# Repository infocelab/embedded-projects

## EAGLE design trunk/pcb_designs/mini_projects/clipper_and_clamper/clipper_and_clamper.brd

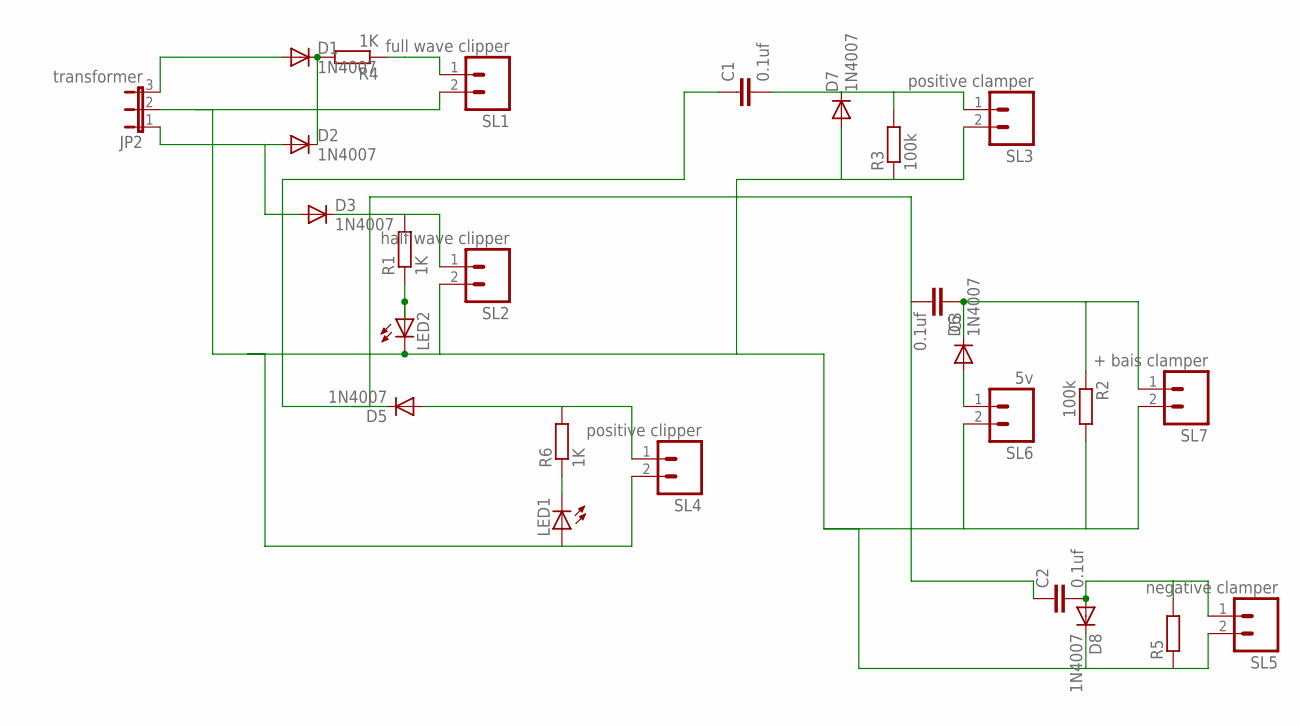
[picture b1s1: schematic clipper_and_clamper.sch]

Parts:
C1, C2, C3: 0.1uf; C2.5-3
D1, D2, D3, D5, D6, D7, D8: 1N4007; DO41-10
JP2: transformer; JP2
LED1, LED2: LED3MM
R1, R4, R6: 1K; 0204/7
R2, R3: 100k; 0204/7
R5: R0204/7; 0204/7
SL1: full wave clipper; 02P
SL2: half wave clipper; 02P
SL3: positive clamper; 02P
SL4: positive clipper; 02P
SL5: negative clamper; 02P
SL6: 5v; 02P
SL7: + bais clamper; 02P

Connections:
unnamed: D1.C, D2.C, R4.2
unnamed: D1.A, JP2.3
unnamed: C1.1, C2.1, C3.2, D2.A, D3.A, D5.C, JP2.1
unnamed: D7.A, D8.C, JP2.2, LED1.A, LED2.K (C), R2.2, R3.1, R5.1, SL1.2, SL2.2, SL3.2, SL4.2, SL5.2, SL6.2, SL7.2
unnamed: R4.1, SL1.1
unnamed: D3.C, R1.2, SL2.1
unnamed: LED2.A, R1.1
unnamed: C2.2, D8.A, R5.2, SL5.1
unnamed: D5.A, R6.2, SL4.1
unnamed: LED1.K (C), R6.1
unnamed: C1.2, D7.C, R3.2, SL3.1
unnamed: D6.A, SL6.1
unnamed: C3.1, D6.C, R2.1, SL7.1

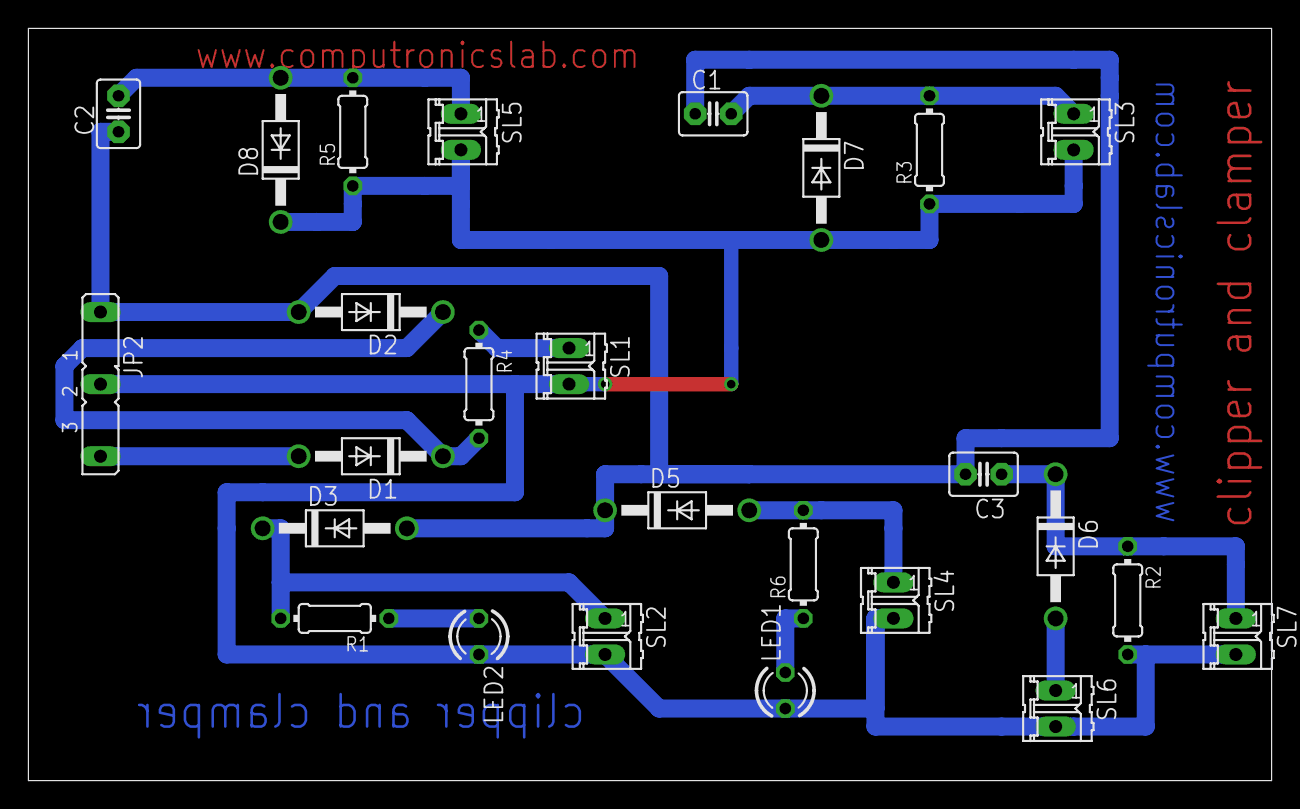
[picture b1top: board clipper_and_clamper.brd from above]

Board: 2 copper layers, 87.6 x 53.0 mm, 26 parts (0 on the bottom side), 13 nets.

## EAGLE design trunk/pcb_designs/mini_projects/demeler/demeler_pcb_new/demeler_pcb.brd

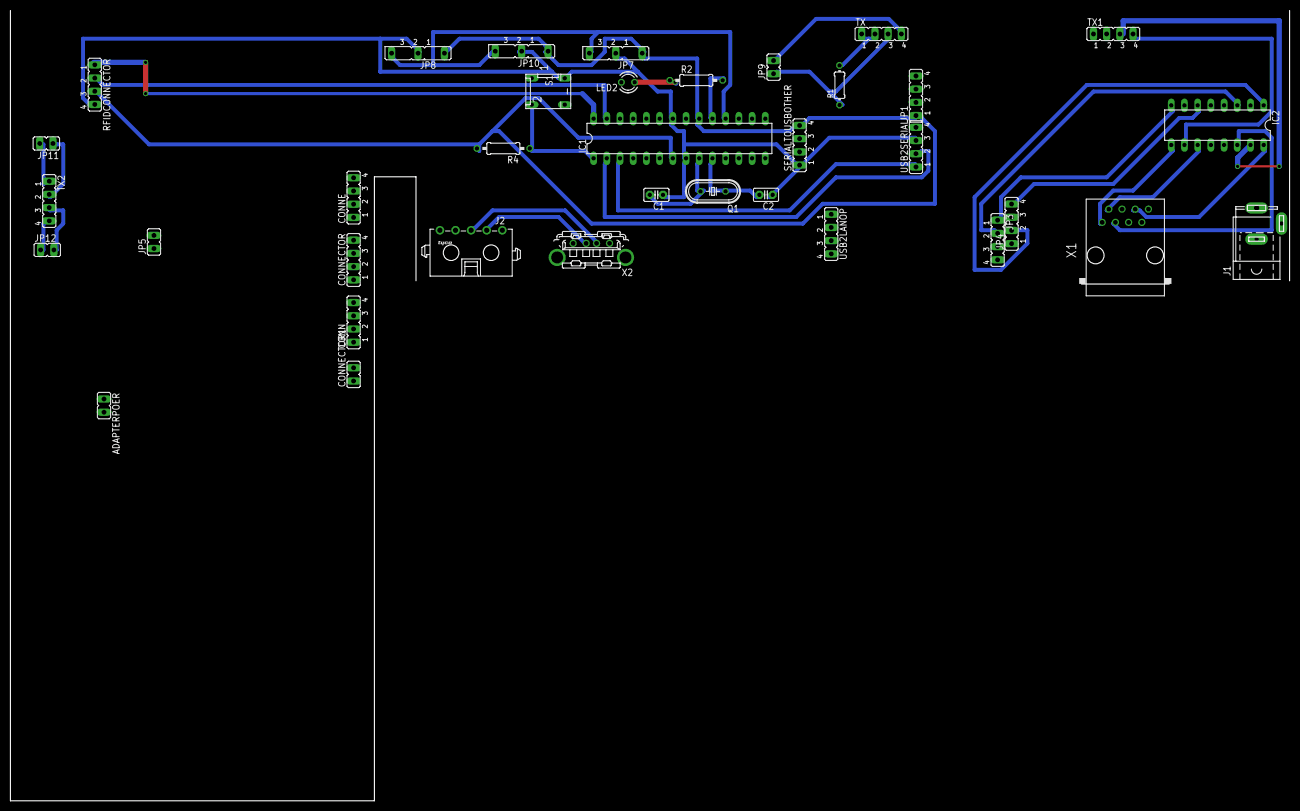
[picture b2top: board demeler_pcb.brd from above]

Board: 2 copper layers, 246.0 x 152.0 mm, 36 parts (0 on the bottom side), 31 nets.

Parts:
ADAPTERPOER: JP1
C1, C2: 22pf; C2.5-2
CONN: JP4
CONNE: JP4
CONNECTOR: JP4
CONNECTOR1: JP1
IC1: ATMEGA328; DIL28-3
IC2: L293D; DIL16
J1: SPC4077
J2: 1445055-5
JP1, JP3, JP4: JP4
JP5, JP9, JP11, JP12: JP1
JP7, JP8, JP10: JP2
LED2: LED3MM
Q1: 16MHZ; HC49/S
R1: 0204/7
R2: 330R; 0207/10
R4: 10K; 0207/10
RFIDCONNECTOR: JP4
S1: DP-02
SERIALTOUSBOTHER: JP4
TX, TX1, TX2: JP4
USB2LANOP, USB2SERIAL: JP4
X1: RJ45-6X; RJ45-NO-SHIELD
X2: KUSBVX

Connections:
+5V: IC1.7, IC1.20, JP1.1, JP7.1, JP8.1, JP10.1, R4.2, RFIDCONNECTOR.3, SERIALTOUSBOTHER.4
GND: C1.1, C2.1, IC1.8, IC1.22, JP7.2, JP8.2, JP10.2, LED2.K, RFIDCONNECTOR.4, S1.4, SERIALTOUSBOTHER.1, USB2SERIAL.3
unnamed: C1.2, IC1.9, Q1.2
unnamed: C2.2, IC1.10, Q1.1
unnamed: IC1.3, USB2SERIAL.1
unnamed: J2.3, X2.3
unnamed: IC1.19, R2.2
unnamed: IC2.9, X1.1
unnamed: IC2.11, X1.2
unnamed: IC2.14, X1.3
unnamed: IC2.16, X1.6
unnamed: IC2.8, JP3.1
unnamed: IC2.6, JP4.4
unnamed: IC2.3, JP3.2
unnamed: IC2.1, JP4.2
unnamed: IC2.10, TX1.4
unnamed: IC2.15, TX1.3
unnamed: IC1.2, USB2SERIAL.2
unnamed: R1.2, TX.1, TX.2
unnamed: JP9.1, R1.1, TX.3
unnamed: J2.2, X2.2
unnamed: JP9.2, TX.4
unnamed: IC1.27, RFIDCONNECTOR.2
unnamed: IC1.28, RFIDCONNECTOR.1
unnamed: IC1.18, JP7.3, JP8.3, JP10.3
unnamed: JP11.2, TX2.1
unnamed: JP11.1, TX2.2
unnamed: JP12.2, TX2.3
unnamed: JP12.1, TX2.4
unnamed: IC1.1, R4.1, S1.2
unnamed: LED2.A, R2.1

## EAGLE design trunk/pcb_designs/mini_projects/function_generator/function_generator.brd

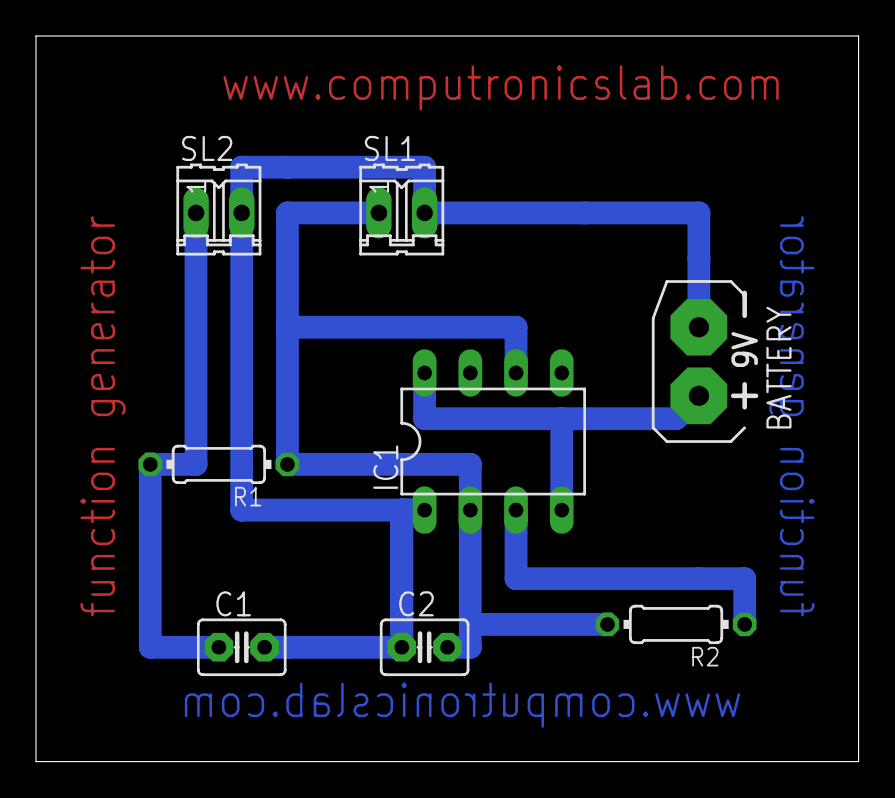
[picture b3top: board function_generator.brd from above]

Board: 2 copper layers, 45.7 x 40.3 mm, 8 parts (0 on the bottom side), 5 nets.

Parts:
BATTERY: 9v; AB9V
C1: .2uf; C2.5-3
C2: .1uf; C2.5-3
IC1: NE555; DIL-08
R1: 100K; 0204/7
R2: 47K; 0204/7
SL1: square wave; 02P
SL2: triangle wave; 02P

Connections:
unnamed: BATTERY.+, IC1.4, IC1.8
unnamed: C2.2, IC1.2, IC1.6, R1.1, R2.2, SL1.1
unnamed: BATTERY.-, C1.2, C2.1, IC1.1, SL1.2, SL2.2
unnamed: IC1.3, R2.1
unnamed: C1.1, R1.2, SL2.1

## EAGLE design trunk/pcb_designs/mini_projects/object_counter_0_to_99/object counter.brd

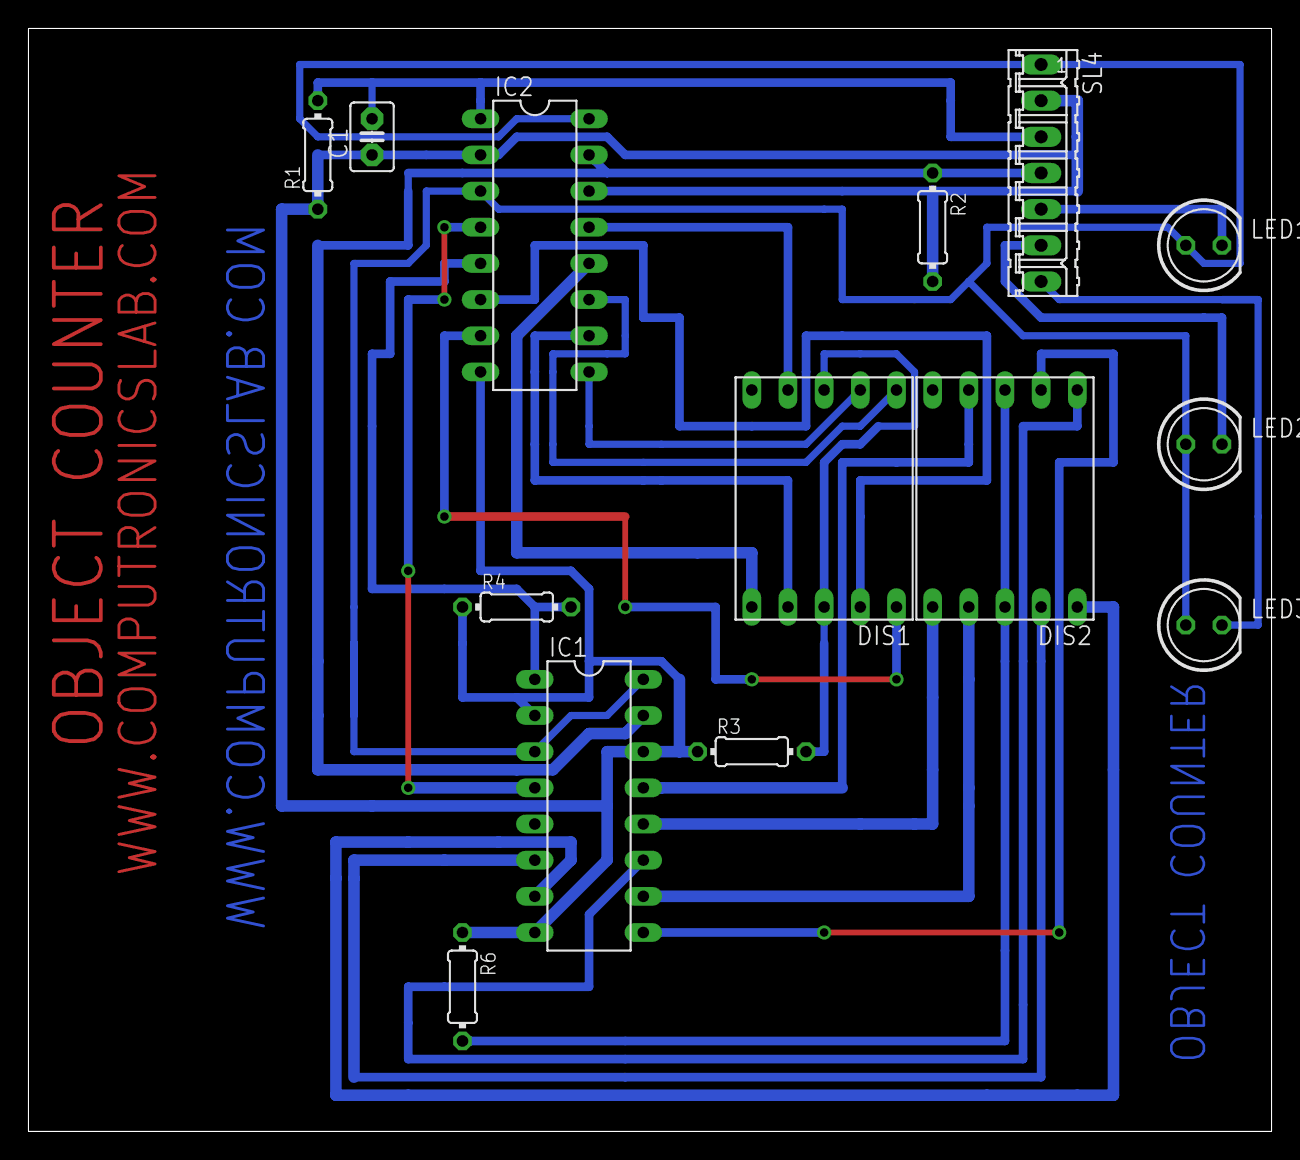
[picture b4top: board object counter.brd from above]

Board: 2 copper layers, 87.3 x 77.5 mm, 14 parts (0 on the bottom side), 25 nets.

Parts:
C1: C2.5-3
DIS1, DIS2: COMMON CATHODE; HDSP-M
IC1, IC2: 4033; DIL16
LED1, LED2, LED3: LED5MM
R1, R4: 33K; 0204/7
R2: 47K; 0204/7
R3, R6: 470E; 0204/7
SL4: 07P

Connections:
unnamed: C1.1, IC1.2, IC1.8, IC1.14, IC2.2, IC2.8, IC2.14, R1.1, R2.2, R3.1, R4.1, R6.1, SL4.2
unnamed: DIS1.3, DIS1.8, R3.2
unnamed: C1.2, IC2.1, R1.2, SL4.3
unnamed: DIS1.7, IC2.10
unnamed: DIS1.6, IC2.12
unnamed: DIS1.4, IC2.13
unnamed: DIS1.2, IC2.9
unnamed: DIS1.1, IC2.11
unnamed: DIS1.9, IC2.6
unnamed: DIS1.10, IC2.7
unnamed: IC1.15, IC2.15, R2.1, SL4.4
unnamed: IC1.3, IC1.16, IC2.3, IC2.16, LED1.A, LED2.A, LED3.A, SL4.1
unnamed: DIS2.3, DIS2.8, R6.2
unnamed: IC1.1, IC2.5, R4.2
unnamed: DIS2.7, IC1.10
unnamed: DIS2.6, IC1.12
unnamed: DIS2.4, IC1.13
unnamed: DIS2.2, IC1.9
unnamed: DIS2.1, IC1.11
unnamed: DIS2.9, IC1.6
unnamed: DIS2.10, IC1.7
unnamed: LED1.K, SL4.5
unnamed: LED2.K, SL4.6
unnamed: LED3.K, SL4.7
V-: IC1.4, IC2.4

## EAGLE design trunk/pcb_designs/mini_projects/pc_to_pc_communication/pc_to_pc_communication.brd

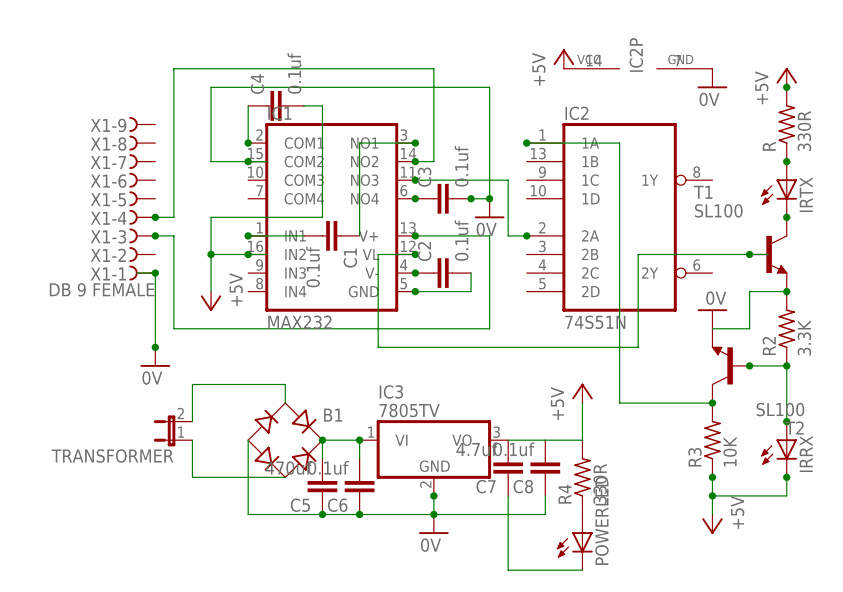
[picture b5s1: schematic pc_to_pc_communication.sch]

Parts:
B1: B-DIL
C1, C2, C3, C4, C6, C8: 0.1uf; C2.5-3
C5: 470uf; C2.5-3
C7: 4.7uf; C2.5-3
IC1: MAX232; DIL16
IC2: 74S51N; DIL14
IC3: 7805TV; TO220V
IRRX: LED3MM
IRTX: LED3MM
POWERLED: LED3MM
R, R4: 330R; 0204/7
R2: 3.3K; 0204/7
R3: 10K; 0204/7
T1, T2: SL100; TO5
TRANSFORMER: JP1E; JP1
X1: DB 9 FEMALE; H2M09ST

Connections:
0V: B1.-, C3.2, C5.1, C6.1, C7.1, C8.1, IC1.15 (COM2), IC2.7 (GND), IC3.2 (GND), POWERLED.K (C), R2.2, T1.1 (E), T2.1 (E), X1.1
+5V: C4.2, C7.2, C8.2, IC1.16 (IN2), IC2.14 (VCC), IC3.3 (VO), IRRX.K (C), R.2, R3.1, R4.2
unnamed: C1.2, IC1.1 (IN1)
unnamed: C1.1, IC1.3 (NO1)
unnamed: C2.1, IC1.4 (V-)
unnamed: C2.2, IC1.5 (GND)
unnamed: C3.1, IC1.6 (NO4)
unnamed: IRTX.K (C), T1.3 (C)
unnamed: C4.1, IC1.2 (COM1)
unnamed: IRTX.A, R.1
unnamed: IC1.13 (V+), X1.3
unnamed: IC1.14 (NO2), X1.4
unnamed: IC1.11 (NO3), IC2.2 (2A)
unnamed: IC1.12 (VL), T1.2 (B)
unnamed: IRRX.A, R2.1, T2.2 (B)
unnamed: IC2.1 (1A), R3.2, T2.3 (C)
unnamed: B1.+, C5.2, C6.2, IC3.1 (VI)
unnamed: B1.AC1, TRANSFORMER.2
unnamed: B1.AC2, TRANSFORMER.1
unnamed: POWERLED.A, R4.1

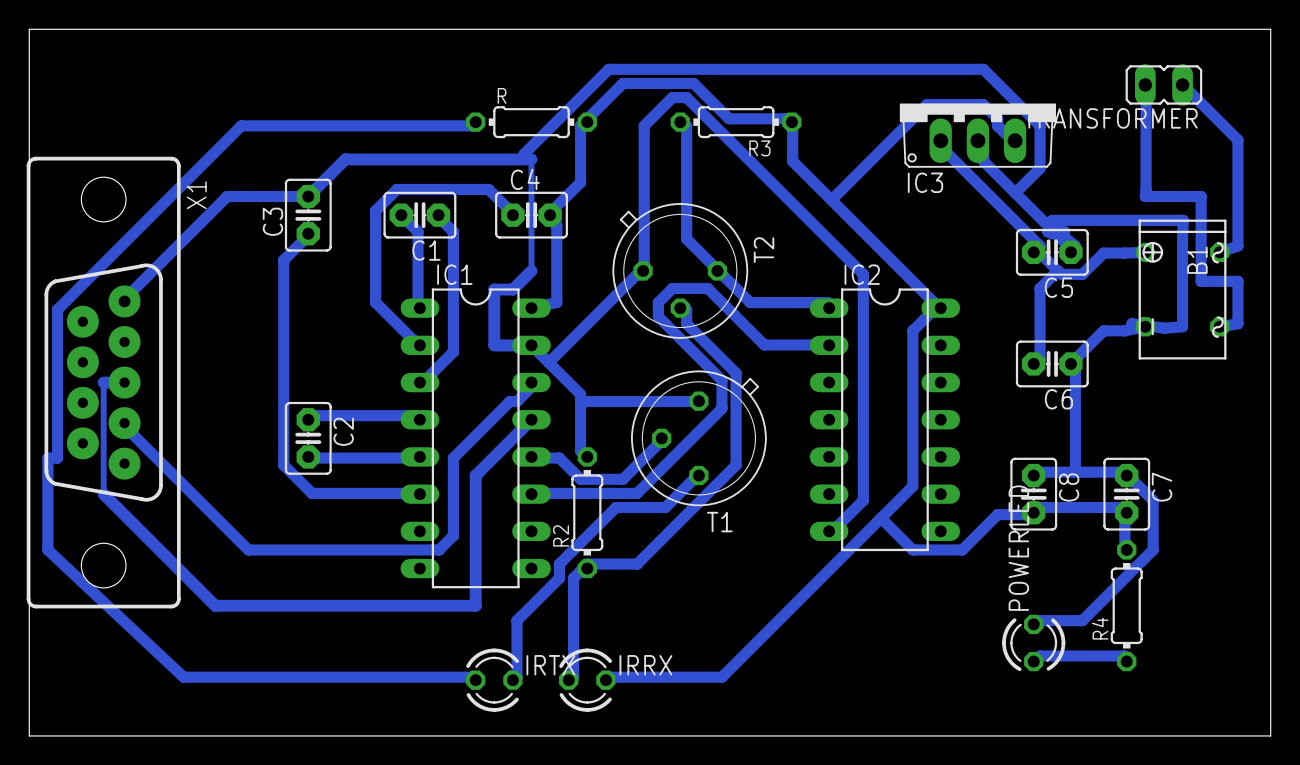
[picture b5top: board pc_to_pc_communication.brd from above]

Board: 2 copper layers, 84.8 x 48.2 mm, 23 parts (0 on the bottom side), 20 nets.

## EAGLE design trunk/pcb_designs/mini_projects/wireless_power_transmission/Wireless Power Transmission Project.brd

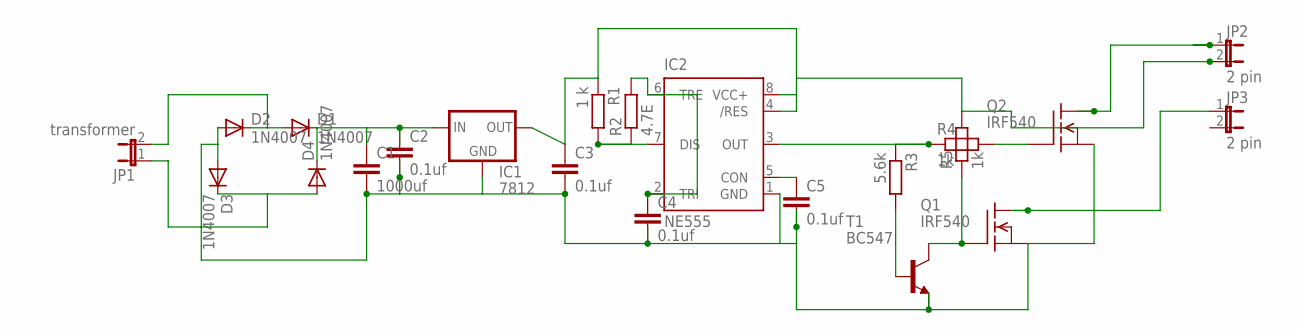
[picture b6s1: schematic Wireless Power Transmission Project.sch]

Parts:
C1: 1000uf; C2.5-5
C2, C3, C4: 0.1uf; C2.5-5
C5: 0.1uf; C2.5-3
D1, D2, D3, D4: 1N4007; DO41-10
IC1: 7812; 78XXL
IC2: NE555; DIL-08
JP1: transformer; JP1
JP2, JP3: 2 pin; JP1
Q1, Q2: IRF540; TO220
R1: 1 k; 0204/7
R2: 4.7E; 0204/7
R3: 5.6k; 0204/7
R4, R5: 1k; 0204/7
T1: BC547; TO92

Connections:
unnamed: D1.A, D2.C, JP1.2
unnamed: C1.2, C2.2, C3.2, C4.2, C5.2, D2.A, D3.A, IC1.GND, IC2.1 (GND), Q1.3 (S), Q2.3 (S), T1.1 (E)
unnamed: D3.C, D4.A, JP1.1
unnamed: C1.1, C2.1, D1.C, D4.C, IC1.IN
unnamed: C5.1, IC2.5 (CON)
unnamed: IC2.3 (OUT), R3.1, R4.1
unnamed: C3.1, IC1.OUT, IC2.4 (/RES), IC2.8 (VCC+), JP2.2, R1.1, R5.2
unnamed: IC2.7 (DIS), R1.2, R2.1
unnamed: R3.2, T1.2 (B)
unnamed: C4.1, IC2.2 (TRI), IC2.6 (TRE), R2.2
unnamed: Q1.1 (G), R5.1, T1.3 (C)
unnamed: Q2.1 (G), R4.2
unnamed: JP2.1, Q2.2 (D)
unnamed: JP3.1, Q1.2 (D)

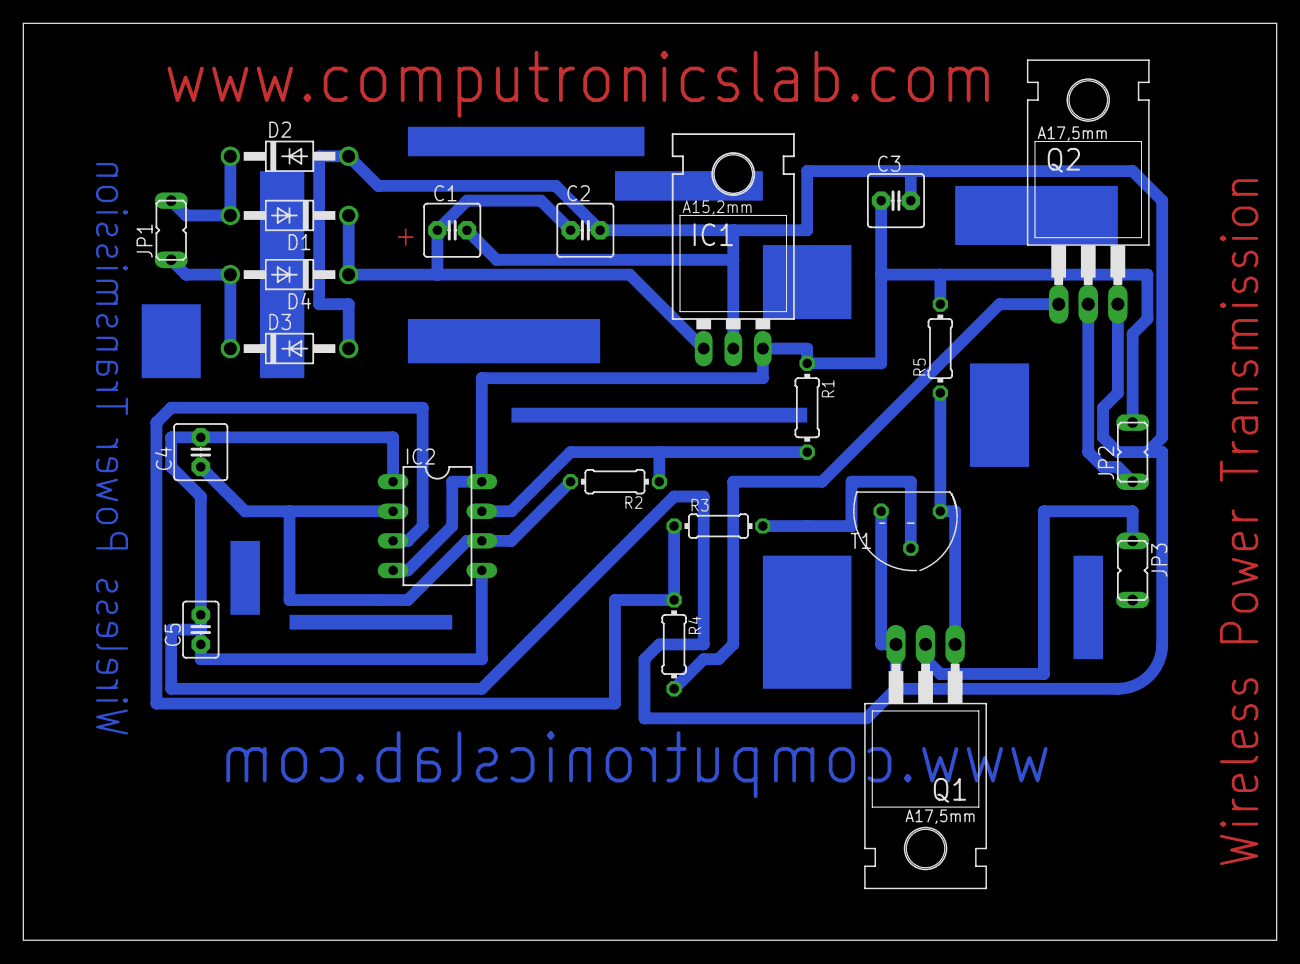
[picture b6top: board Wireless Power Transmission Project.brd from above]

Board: 2 copper layers, 107.6 x 78.7 mm, 22 parts (0 on the bottom side), 14 nets.

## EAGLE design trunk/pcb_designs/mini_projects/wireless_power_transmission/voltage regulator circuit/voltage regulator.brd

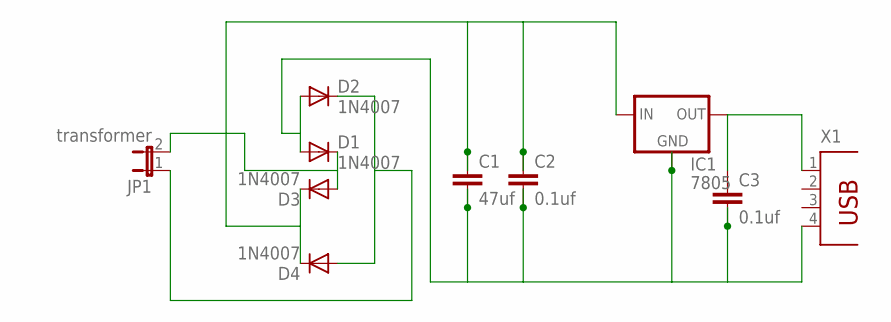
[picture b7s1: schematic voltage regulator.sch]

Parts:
C1: 47uf; C2.5-3
C2, C3: 0.1uf; C2.5-3
D1, D2, D3, D4: 1N4007; DO41-10
IC1: 7805; 78XXL
JP1: transformer; JP1
X1: PN87520

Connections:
unnamed: C1.2, C2.2, C3.2, D1.A, D2.A, IC1.GND, X1.4
unnamed: C1.1, C2.1, D3.C, D4.C, IC1.IN
unnamed: D2.C, D4.A, JP1.1
unnamed: D1.C, D3.A, JP1.2
unnamed: C3.1, IC1.OUT, X1.1

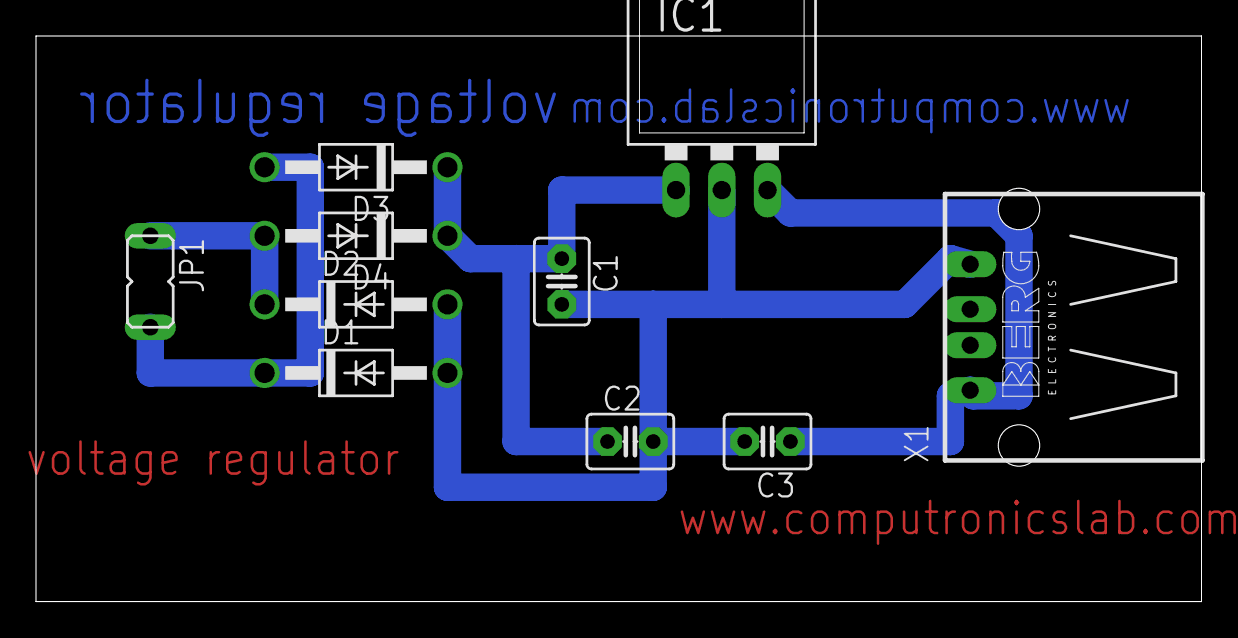
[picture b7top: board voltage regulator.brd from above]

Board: 2 copper layers, 64.8 x 31.4 mm, 10 parts (0 on the bottom side), 5 nets.

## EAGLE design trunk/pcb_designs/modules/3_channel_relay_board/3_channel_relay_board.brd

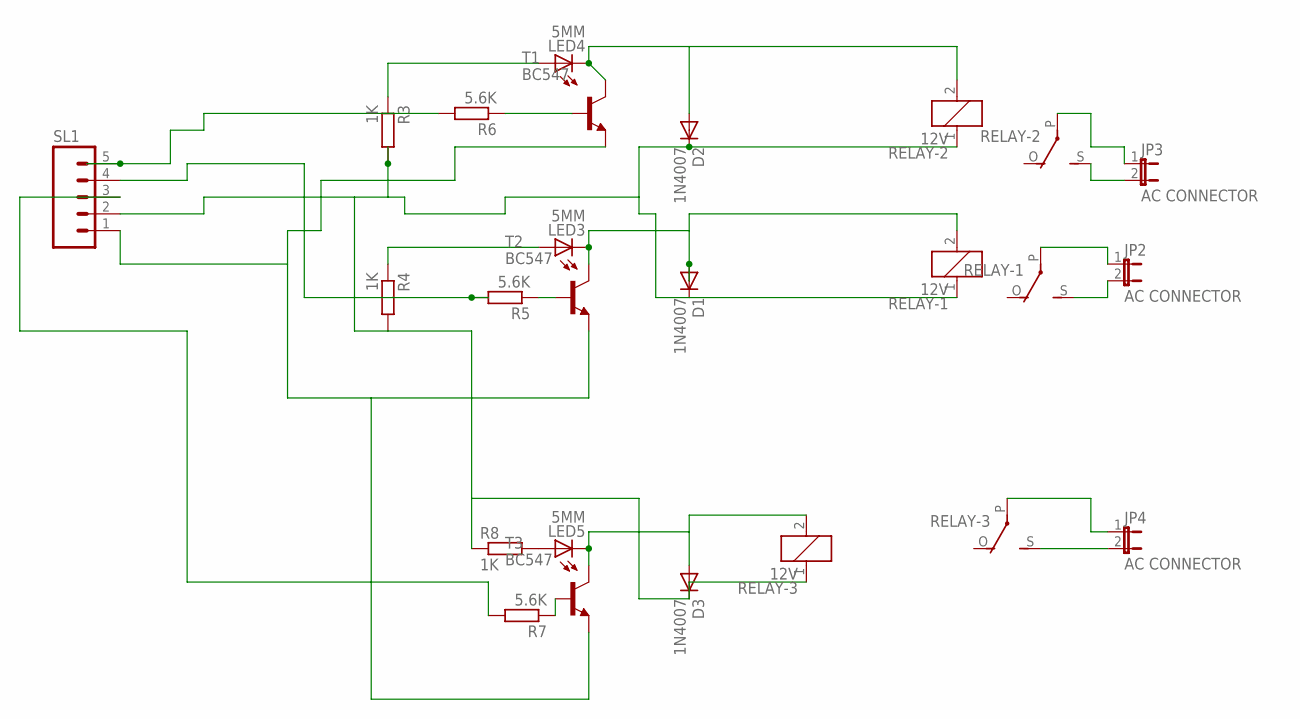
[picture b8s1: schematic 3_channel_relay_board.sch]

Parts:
D1, D2, D3: 1N4007; DO41-10
JP2, JP3, JP4: AC CONNECTOR; JP1
LED3, LED4, LED5: 5MM; LED5MM
R3, R4, R8: 1K; 0204/7
R5, R6, R7: 5.6K; 0204/7
RELAY-1, RELAY-2, RELAY-3: 12V; G5LE
SL1: M05; 05P
T1, T2, T3: BC547; TO92

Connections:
unnamed: D1.A, LED3.K (C), RELAY-1.2, T2.3 (C)
unnamed: SL1.1, T1.1 (E), T2.1 (E), T3.1 (E)
unnamed: R7.2, SL1.3
unnamed: R6.2, SL1.5
unnamed: D1.C, D2.C, D3.C, R3.2, R4.2, R8.1, RELAY-1.1, RELAY-2.1, RELAY-3.1, SL1.2
unnamed: R6.1, T1.2 (B)
unnamed: R5.1, T2.2 (B)
unnamed: LED3.A, R4.1
unnamed: LED4.A, R3.1
unnamed: JP2.2, RELAY-1.S
unnamed: JP2.1, RELAY-1.P
unnamed: JP3.1, RELAY-2.P
unnamed: R5.2, SL1.4
unnamed: D2.A, LED4.K (C), RELAY-2.2, T1.3 (C)
unnamed: JP3.2, RELAY-2.S
unnamed: D3.A, LED5.K (C), RELAY-3.2, T3.3 (C)
unnamed: R7.1, T3.2 (B)
unnamed: LED5.A, R8.2
unnamed: JP4.1, RELAY-3.P
unnamed: JP4.2, RELAY-3.S

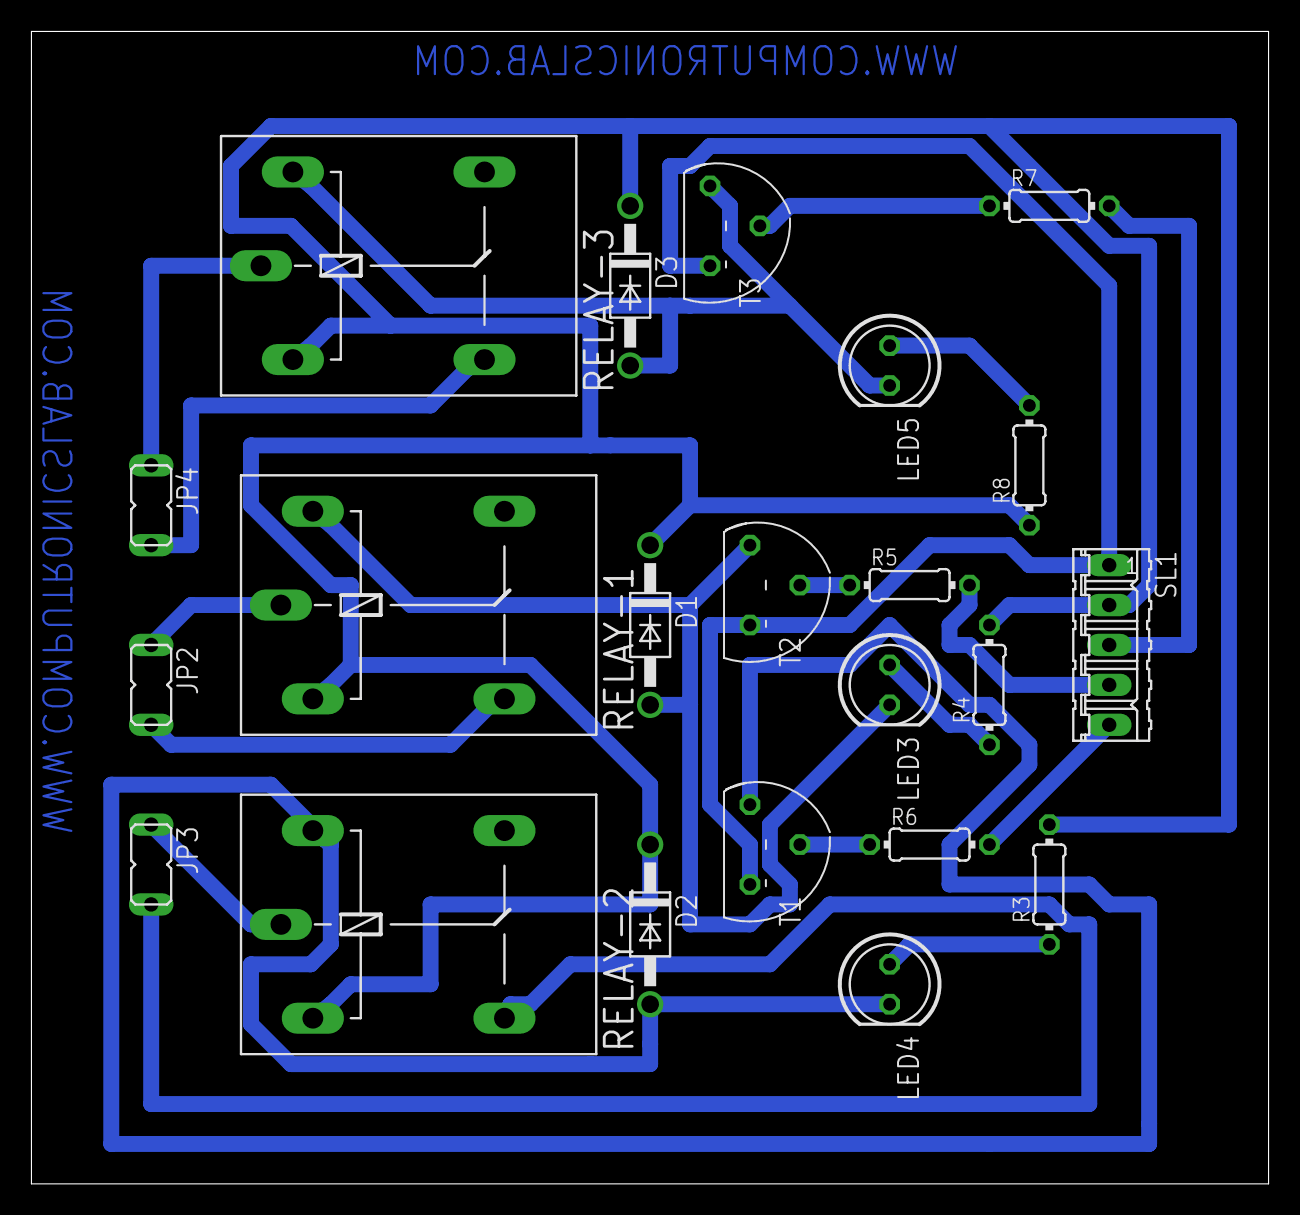
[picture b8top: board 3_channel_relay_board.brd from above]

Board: 2 copper layers, 78.7 x 73.3 mm, 22 parts (0 on the bottom side), 20 nets.
